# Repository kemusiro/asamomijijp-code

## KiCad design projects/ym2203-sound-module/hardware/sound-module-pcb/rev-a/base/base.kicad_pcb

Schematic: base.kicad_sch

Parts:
A1: Raspberry Pi Pico 2; A1
A2: AE-PCM5102A / I2S 48kHz; A2
C1: 47u 10V; C1
C2: 10u 10V; C2
C3: 100n; C3
C4: 100n; C4
C5: 2.2u X7R 10V; C5
C6: 2.2u X7R 10V; C6
C7: 1u X7R 10V; C7
C8: 100n; C8
C9: 100n; C9
C10: 100n; C10
C11: 10u 10V; C11
C12: 10u 10V; C12
C13: 10u 10V; C13
C14: 2.2n C0G; C14
C15: 2.2n C0G; C15
C16: 10u 10V; C16
C17: 100n; C17
C18: 100n; C18
C19: 4.7u BP 10V; C19
C20: 4.7u BP 10V; C20
C21: 47p; C21
C22: 4.7u BP 10V; C22
C23: 4.7u BP 10V; C23
C24: 47p; C24
C25: 100n; C25
C26: 4.7u BP 10V; C26
C27: 4.7u BP 10V; C27
D1: SS14 / A=+5V K=VSYS; D1
F1: PTC 0.5A hold; F1
H1: M3 / 3.2mm NPTH; H1
H2: M3 / 3.2mm NPTH; H2
H3: M3 / 3.2mm NPTH; H3
H4: M3 / 3.2mm NPTH; H4
H5: M3 / 3.2mm NPTH; H5
H6: M3 / 3.2mm NPTH; H6
H7: M3 / 3.2mm NPTH; H7
JHOST: HOST 3.3V I2C; JHOST
JLINE: TRS JACK / AMS-22 LINE IN; JLINE
JMOD: ESQ-125-58-L-D / socket; JMOD
JPOWER: MAIN INPUT / REGULATED DC 5V; JPOWER
JRUN: RESET SWITCH; JRUN
JVOL: EXTERNAL DUAL 10k A POT; JVOL
Q1: MMBT3904 / B1 E2 C3; Q1
R1: 4.7k; R1
R2: 4.7k; R2
R3: 4.7k; R3
R4: 4.7k; R4
R5: 10k; R5
R6: 47; R6
R7: 47; R7
R8: 47; R8
R9: 470; R9
R10: 470; R10
R11: 10k 1%; R11
R12: 10k 1%; R12
R13: 100k 1%; R13
R14: 100k 1%; R14
R15: 22k 1%; R15
R16: 100k 1%; R16
R17: 100k 1%; R17
R18: 22k 1%; R18
R19: 10k; R19
R20: 100k; R20
R21: 10k; R21
R22: 100k; R22
R23: 100; R23
R24: 100k; R24
R25: 100; R25
RN1: RKC8BD103J; RN1
RN2: RKC8BD103J; RN2
RN3: RKC4BD103J; RN3
RN4: RKC4BD103J; RN4
RN5: RKC4BD103J; RN5
TP1: +5V; TP1
TP2: +3V3; TP2
TP3: GND; TP3
TP4: ARM; TP4
TP5: RESET_N; TP5
TP6: AUX_SDA; TP6
TP7: AUX_SCL; TP7
TP8: DAC_L; TP8
TP9: DAC_R; TP9
TP10: VREF; TP10
TP11: MIX_L; TP11
TP12: MIX_R; TP12
U1: MCP23017-E/SP / 0x20; U1
U2: TC74HC08AP / 3.3V; U2
U3: MCP6022-I/P / reference; U3
U4: MCP6022-I/P / stereo mixer; U4
U5: CD74HC4053E / line mute; U5

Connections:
/+3V3: A1.36 (3V3 OUT), A2.1 (CPVDD), A2.8 (AVDD), A2.20 (DVDD), C2.1, C3.1, C4.1, C8.1, C9.1, C10.1, C11.1, C12.1, C13.1, JMOD.5 (+3V3), R1.2, R2.2, R3.2, R4.2, RN3.1 (COM), RN4.1 (COM), TP2.1, U1.9 (VDD), U2.14 (VCC)
/+5V: C1.1, C17.1, C18.1, C25.1, D1.2 (A), F1.2, JMOD.1 (+5V), JMOD.3 (+5V), R11.1, R21.1, TP1.1, U3.8 (VDD), U4.8 (VDD), U5.16 (VCC)
/A0: A1.11 (GP8 / A0), JMOD.15 (A0), RN2.3 (R2)
/A1: A1.12 (GP9 / A1), JMOD.17 (A1), RN2.4 (R3)
/ANALOG_L: C20.1, JMOD.42 (ANALOG_L)
/ANALOG_R: C23.1, JMOD.44 (ANALOG_R)
/ARM: A1.29 (GP22 / ARM), JMOD.24 (ARM), RN2.2 (R1), TP4.1, U2.1 (1A), U2.4 (2A), U2.9 (3A)
/AUX0: JMOD.39 (AUX0), RN2.8 (R7), U1.25 (GPA4)
/AUX1: JMOD.40 (AUX1), RN2.9 (R8), U1.26 (GPA5)
/AUX_SCL: A1.32 (GP27 / AUX_SCL), JMOD.33 (AUX_SCL), R4.1, TP7.1, U1.12 (SCL)
/AUX_SDA: A1.31 (GP26 / AUX_SDA), JMOD.32 (AUX_SDA), R3.1, TP6.1, U1.13 (SDA)
/CAPM: A2.4 (CAPM), C5.2
/CAPP: A2.2 (CAPP), C5.1
/CS_N: A1.17 (GP13 / CS_N), JMOD.19 (CS_N), RN4.2 (R1)
/D0: A1.1 (GP0 / D0), JMOD.7 (D0), RN1.2 (R1)
/D1: A1.2 (GP1 / D1), JMOD.8 (D1), RN1.3 (R2)
/D2: A1.4 (GP2 / D2), JMOD.9 (D2), RN1.4 (R3)
/D3: A1.5 (GP3 / D3), JMOD.10 (D3), RN1.5 (R4)
/D4: A1.6 (GP4 / D4), JMOD.11 (D4), RN1.6 (R5)
/D5: A1.7 (GP5 / D5), JMOD.12 (D5), RN1.7 (R6)
/D6: A1.9 (GP6 / D6), JMOD.13 (D6), RN1.8 (R7)
/D7: A1.10 (GP7 / D7), JMOD.14 (D7), RN1.9 (R8)
/DAC_ALLOW: RN2.6 (R5), U1.24 (GPA3), U2.5 (2B)
/DAC_BCK: A2.13 (BCK), R7.2
/DAC_DIN: A2.14 (DIN), R6.2
/DAC_L: A2.6 (OUTL), R9.1, TP8.1
/DAC_LRCK: A2.15 (LRCK), R8.2
/DAC_R: A2.7 (OUTR), R10.1, TP9.1
/DAC_XSMT: A2.17 (XSMT), R5.1, U2.6 (2Y)
/EXT_5V: F1.1, JPOWER.1 (EXT_5V)
/FM_AC_L: C19.2, R13.1
/FM_AC_R: C22.2, R16.1
/FM_CLK: A1.22 (GP17 / FM_CLK), JMOD.28 (FM_CLK), RN5.3 (R2)
/FM_L: C14.1, C19.1, R9.2
/FM_R: C15.1, C22.1, R10.2
/FM_SD: A1.21 (GP16 / FM_SD), JMOD.27 (FM_SD), RN5.2 (R1)
/FM_SH1: A1.24 (GP18 / FM_SH1), JMOD.29 (FM_SH1), RN5.4 (R3)
/FM_SH2: A1.25 (GP19 / FM_SH2), JMOD.30 (FM_SH2), RN5.5 (R4)
/GND: A1.3 (GND), A1.8 (GND), A1.13 (GND), A1.18 (GND), A1.23 (GND), A1.28 (GND), A1.33 (GND), A1.38 (GND), A2.3 (CPGND), A2.9 (AGND), A2.10 (DEMP), A2.11 (FLT), A2.12 (SCK), A2.16 (FMT), A2.19 (DGND), C1.2, C2.2, C3.2, C4.2, C6.2, C7.2, C8.2, C9.2, C10.2, C11.2, C12.2, C13.2, C14.2, C15.2, C16.2, C17.2, C18.2, C25.2, JHOST.1 (GND), JHOST.4 (GND), JLINE.3 (GND), JMOD.2 (GND), JMOD.4 (GND), JMOD.6 (GND), JMOD.16 (GND), JMOD.18 (GND), JMOD.22 (GND), JMOD.26 (GND), JMOD.31 (GND), JMOD.34 (GND), JMOD.41 (GND), JMOD.43 (GND), JMOD.45 (GND), JMOD.48 (GND), JMOD.49 (GND), JPOWER.2 (GND), JRUN.2 (GND), JVOL.3 (GND), JVOL.6 (GND), Q1.2 (E), R5.2, R12.2, R20.2, R22.2, R24.2, RN1.1 (COM), RN2.1 (COM), RN5.1 (COM), TP3.1, U1.5 (GPB4), U1.6 (GPB5), U1.7 (GPB6), U1.10 (VSS), U1.15 (A0), U1.16 (A1), U1.17 (A2), U2.7 (GND), U2.12 (4A), U2.13 (4B), U3.4 (VSS), U4.4 (VSS), U5.3 (Z1), U5.5 (Z0), U5.6 (INH), U5.7 (VEE), U5.8 (GND), U5.9 (C)
/HOST_SCL: A1.27 (GP21 / HOST_SCL), JHOST.3 (HOST_SCL), R2.1
/HOST_SDA: A1.26 (GP20 / HOST_SDA), JHOST.2 (HOST_SDA), R1.1
/I2S_BCLK: A1.15 (GP11 / I2S_BCLK), R7.1
/I2S_DATA: A1.14 (GP10 / I2S_DATA), R6.1
/I2S_LRCK: A1.16 (GP12 / I2S_LRCK), R8.1
/ID0: JMOD.35 (ID0), RN3.2 (R1), U1.1 (GPB0)
/ID1: JMOD.36 (ID1), RN3.3 (R2), U1.2 (GPB1)
/ID2: JMOD.37 (ID2), RN3.4 (R3), U1.3 (GPB2)
/LDOO: A2.18 (LDOO), C7.1
/LINE_ALLOW: RN2.7 (R6), U1.22 (GPA1), U2.10 (3B)
/LINE_L: JLINE.1 (LINE_L), R23.2
/LINE_R: JLINE.2 (LINE_R), R25.2
/LINE_RUN: R19.1, U2.8 (3Y)
/MIX_L: C21.1, R15.1, TP11.1, U4.1 (OUTA), U5.12 (X0)
/MIX_R: C24.1, R18.1, TP12.1, U4.7 (OUTB), U5.2 (Y0)
/MOD_AC_L: C20.2, R14.1
/MOD_AC_R: C23.2, R17.1
/MUTED_L: C26.1, U5.14 (X)
/MUTED_R: C27.1, U5.15 (Y)
/MUTE_5V: Q1.3 (C), R21.2, U5.10 (B), U5.11 (A)
/MUTE_BASE: Q1.1 (B), R19.2, R20.1
/OUT_AC_L: C26.2, JVOL.1 (OUT_AC_L), R22.1
/OUT_AC_R: C27.2, JVOL.4 (OUT_AC_R), R24.1
/PICO_RUN: A1.30 (RUN), JRUN.1 (PICO_RUN), U1.18 (RESET_N)
/PRESENT_N: JMOD.38 (PRESENT_N), RN3.5 (R4), U1.4 (GPB3)
/RD_N: A1.20 (GP15 / RD_N), JMOD.21 (RD_N), RN4.4 (R3)
/REF_RAW: C16.1, R11.2, R12.1, U3.3 (INA+)
/REF_SPARE: U3.6 (INB-), U3.7 (OUTB)
/RESET_N: JMOD.23 (RESET_N), TP5.1, U2.3 (1Y)
/RESET_RELEASE: RN2.5 (R4), U1.21 (GPA0), U2.2 (1B)
/STATUS: A1.34 (GP28 / STATUS), JMOD.25 (STATUS), RN4.5 (R4)
/SUM_L: C21.2, R13.2, R14.2, R15.2, U4.2 (INA-)
/SUM_R: C24.2, R16.2, R17.2, R18.2, U4.6 (INB-)
/VNEG: A2.5 (VNEG), C6.1
/VOL_L: JVOL.2 (VOL_L), R23.1
/VOL_R: JVOL.5 (VOL_R), R25.1
/VREF: TP10.1, U3.1 (OUTA), U3.2 (INA-), U3.5 (INB+), U4.3 (INA+), U4.5 (INB+), U5.1 (Y1), U5.13 (X1)
/VSYS: A1.39 (VSYS), D1.1 (K)
/WR_N: A1.19 (GP14 / WR_N), JMOD.20 (WR_N), RN4.3 (R2)

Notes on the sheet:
COMMON BASE / Pico 2 + stereo DAC + line mixer
Rev A / GPIO approved 2026-10-18 / Prototype - hardware untested / See README before manufacture
Labels of the same name are connected. Pin numbers are physical pins. Stereo line output to AMS-22.
CONTROLLER / IO
POWER / SAFETY
MODULE
DAC / CLOCK
ANALOG
PULLS / DECOUPLING / BUS / YM / FM / TEST

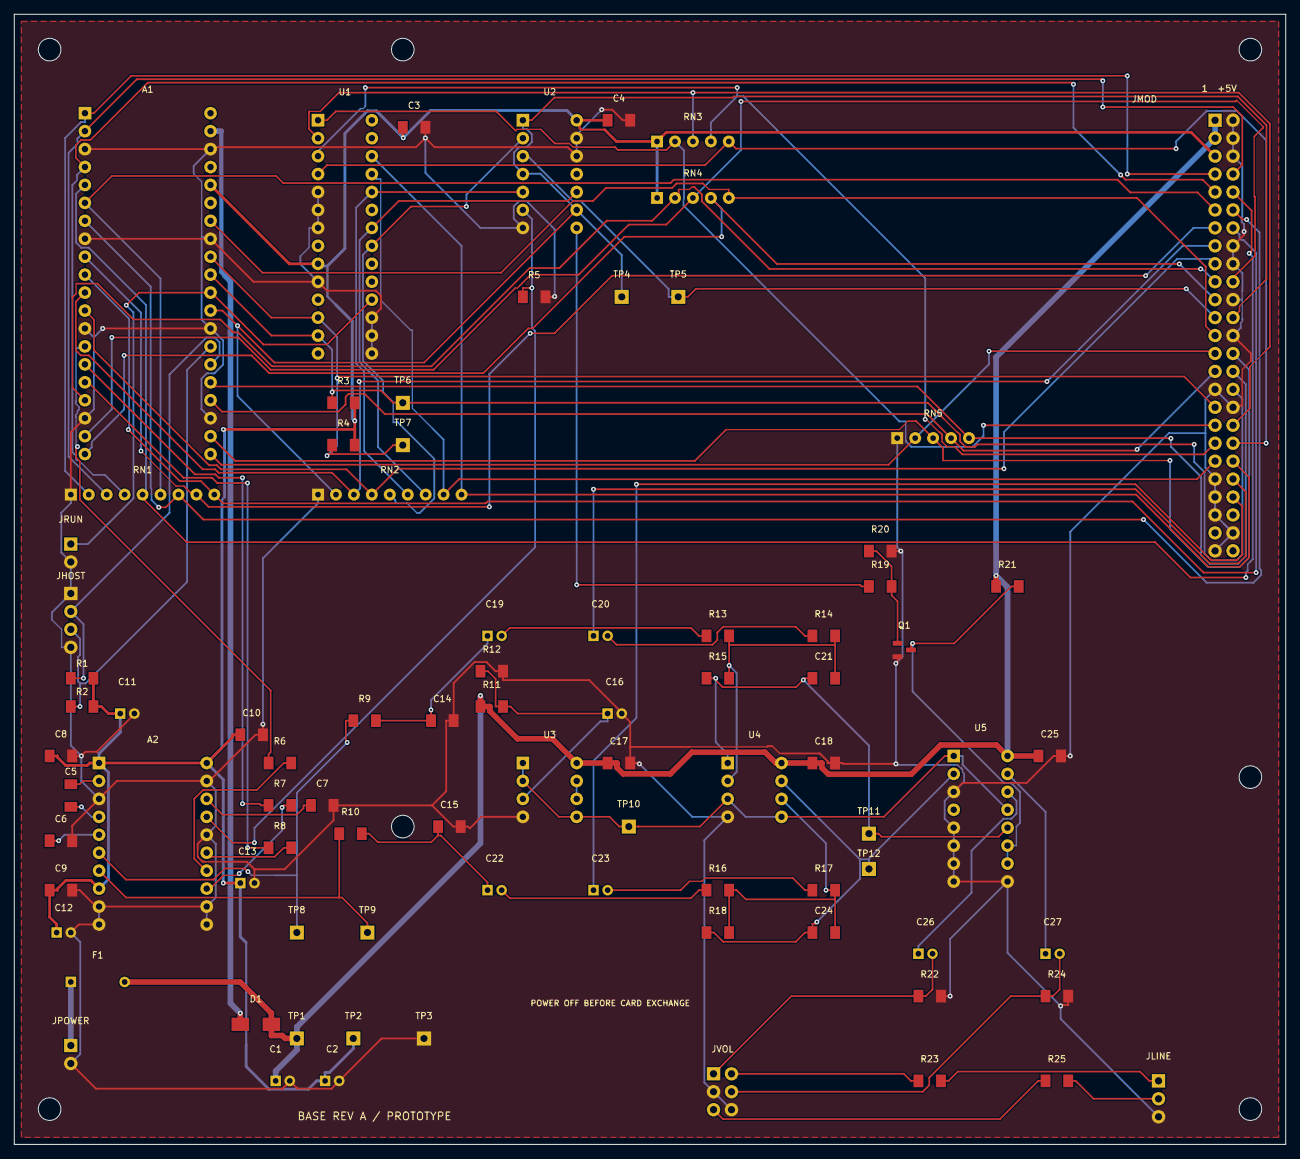
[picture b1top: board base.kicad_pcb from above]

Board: 2 copper layers, 180.0 x 160.0 mm, 92 parts (0 on the bottom side), 78 nets.

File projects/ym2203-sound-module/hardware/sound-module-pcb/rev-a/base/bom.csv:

reference,value,footprint,x_mm,y_mm,source,role
A1,Raspberry Pi Pico 2,SOUNDPCB:A1,10.0,14.0,https://datasheets.raspberrypi.com/pico/pico-2-datasheet.pdf,
JMOD,ESQ-125-58-L-D / socket,SOUNDPCB:JMOD,170.0,15.0,https://suddendocs.samtec.com/catalog_english/esq_th.pdf,Top-side 16.13mm female. Block contact 50 with an insulating key.
JHOST,HOST 3.3V I2C,SOUNDPCB:JHOST,8.0,82.0,,
JPOWER,MAIN INPUT / REGULATED DC 5V,SOUNDPCB:JPOWER,8.0,146.0,,"Required main supply: pin 1 = regulated +5V, pin 2 = GND. No reverse-polarity or overvoltage protection."
F1,PTC 0.5A hold,SOUNDPCB:F1,8.0,137.0,,
D1,SS14 / A=+5V K=VSYS,SOUNDPCB:D1,32.0,143.0,,Prevents Pico USB from feeding the external supply through VSYS
C1,47u 10V,SOUNDPCB:C1,37.0,151.0,,
C2,10u 10V,SOUNDPCB:C2,44.0,151.0,,
JRUN,RESET SWITCH,SOUNDPCB:JRUN,8.0,75.0,,
R1,4.7k,SOUNDPCB:R1,8.0,94.0,,Host pullups removable if already supplied externally
R2,4.7k,SOUNDPCB:R2,8.0,98.0,,Host pullups removable if already supplied externally
R3,4.7k,SOUNDPCB:R3,45.0,55.0,,Host pullups removable if already supplied externally
R4,4.7k,SOUNDPCB:R4,45.0,61.0,,Host pullups removable if already supplied externally
U1,MCP23017-E/SP / 0x20,SOUNDPCB:U1,43.0,15.0,https://akizukidenshi.com/catalog/g/g109486/,
C3,100n,SOUNDPCB:C3,55.0,16.0,,Place immediately beside supply pin
U2,TC74HC08AP / 3.3V,SOUNDPCB:U2,72.0,15.0,https://akizukidenshi.com/catalog/g/g114059/,
C4,100n,SOUNDPCB:C4,84.0,15.0,,Place immediately beside supply pin
RN1,RKC8BD103J,SOUNDPCB:RN1,8.0,68.0,https://akizukidenshi.com/catalog/g/g111910/,
RN2,RKC8BD103J,SOUNDPCB:RN2,43.0,68.0,https://akizukidenshi.com/catalog/g/g111910/,
RN3,RKC4BD103J,SOUNDPCB:RN3,91.0,18.0,https://akizukidenshi.com/catalog/g/g111909/,
RN4,RKC4BD103J,SOUNDPCB:RN4,91.0,26.0,https://akizukidenshi.com/catalog/g/g111909/,
RN5,RKC4BD103J,SOUNDPCB:RN5,125.0,60.0,https://akizukidenshi.com/catalog/g/g111909/,
R5,10k,SOUNDPCB:R5,72.0,40.0,,
A2,AE-PCM5102A / I2S 48kHz,SOUNDPCB:A2,12.0,106.0,https://akizukidenshi.com/catalog/g/g111836/,
R6,47,SOUNDPCB:R6,36.0,106.0,,
R7,47,SOUNDPCB:R7,36.0,112.0,,
R8,47,SOUNDPCB:R8,36.0,118.0,,
C5,2.2u X7R 10V,SOUNDPCB:C5,8.0,109.0,,
C6,2.2u X7R 10V,SOUNDPCB:C6,5.0,117.0,,
C7,1u X7R 10V,SOUNDPCB:C7,42.0,112.0,,
C8,100n,SOUNDPCB:C8,5.0,105.0,,Place immediately beside supply pin
C9,100n,SOUNDPCB:C9,5.0,124.0,,Place immediately beside supply pin
C10,100n,SOUNDPCB:C10,32.0,102.0,,Place immediately beside supply pin
C11,10u 10V,SOUNDPCB:C11,15.0,99.0,,
C12,10u 10V,SOUNDPCB:C12,6.0,130.0,,
C13,10u 10V,SOUNDPCB:C13,32.0,123.0,,
R9,470,SOUNDPCB:R9,48.0,100.0,,
C14,2.2n C0G,SOUNDPCB:C14,59.0,100.0,,
R10,470,SOUNDPCB:R10,46.0,116.0,,
C15,2.2n C0G,SOUNDPCB:C15,60.0,115.0,,
U3,MCP6022-I/P / reference,SOUNDPCB:U3,72.0,106.0,,
R11,10k 1%,SOUNDPCB:R11,66.0,98.0,,
R12,10k 1%,SOUNDPCB:R12,66.0,93.0,,
C16,10u 10V,SOUNDPCB:C16,84.0,99.0,,
C17,100n,SOUNDPCB:C17,84.0,106.0,,Place immediately beside supply pin
U4,MCP6022-I/P / stereo mixer,SOUNDPCB:U4,101.0,106.0,,
C18,100n,SOUNDPCB:C18,113.0,106.0,,Place immediately beside supply pin
C19,4.7u BP 10V,SOUNDPCB:C19,67.0,88.0,,
C20,4.7u BP 10V,SOUNDPCB:C20,82.0,88.0,,
R13,100k 1%,SOUNDPCB:R13,98.0,88.0,,
R14,100k 1%,SOUNDPCB:R14,113.0,88.0,,
R15,22k 1%,SOUNDPCB:R15,98.0,94.0,,
C21,47p,SOUNDPCB:C21,113.0,94.0,,
C22,4.7u BP 10V,SOUNDPCB:C22,67.0,124.0,,
C23,4.7u BP 10V,SOUNDPCB:C23,82.0,124.0,,
R16,100k 1%,SOUNDPCB:R16,98.0,124.0,,
R17,100k 1%,SOUNDPCB:R17,113.0,124.0,,
R18,22k 1%,SOUNDPCB:R18,98.0,130.0,,
C24,47p,SOUNDPCB:C24,113.0,130.0,,
U5,CD74HC4053E / line mute,SOUNDPCB:U5,133.0,105.0,https://akizukidenshi.com/catalog/g/g113266/,
C25,100n,SOUNDPCB:C25,145.0,105.0,,Place immediately beside supply pin
Q1,MMBT3904 / B1 E2 C3,SOUNDPCB:Q1,126.0,90.0,https://www.onsemi.com/pdf/datasheet/mmbt3904lt1-d.pdf,
R19,10k,SOUNDPCB:R19,121.0,81.0,,
R20,100k,SOUNDPCB:R20,121.0,76.0,,
R21,10k,SOUNDPCB:R21,139.0,81.0,,
C26,4.7u BP 10V,SOUNDPCB:C26,128.0,133.0,,
R22,100k,SOUNDPCB:R22,128.0,139.0,,
R23,100,SOUNDPCB:R23,128.0,151.0,,
C27,4.7u BP 10V,SOUNDPCB:C27,146.0,133.0,,
R24,100k,SOUNDPCB:R24,146.0,139.0,,
R25,100,SOUNDPCB:R25,146.0,151.0,,
JVOL,EXTERNAL DUAL 10k A POT,SOUNDPCB:JVOL,99.0,150.0,,Stereo 10k A pot: each channel HIGH/WIPER/LOW. Separate from mute.
JLINE,TRS JACK / AMS-22 LINE IN,SOUNDPCB:JLINE,162.0,151.0,,"External 3.5mm jack module, L=tip R=ring GND=sleeve. Not headphone power output."
TP1,+5V,SOUNDPCB:TP1,40.0,145.0,,
TP2,+3V3,SOUNDPCB:TP2,48.0,145.0,,
TP3,GND,SOUNDPCB:TP3,58.0,145.0,,
TP4,ARM,SOUNDPCB:TP4,86.0,40.0,,
TP5,RESET_N,SOUNDPCB:TP5,94.0,40.0,,
TP6,AUX_SDA,SOUNDPCB:TP6,55.0,55.0,,
TP7,AUX_SCL,SOUNDPCB:TP7,55.0,61.0,,
TP8,DAC_L,SOUNDPCB:TP8,40.0,130.0,,
TP9,DAC_R,SOUNDPCB:TP9,50.0,130.0,,
TP10,VREF,SOUNDPCB:TP10,87.0,115.0,,
TP11,MIX_L,SOUNDPCB:TP11,121.0,116.0,,
TP12,MIX_R,SOUNDPCB:TP12,121.0,121.0,,
H1,M3 / 3.2mm NPTH,SOUNDPCB:H1,55.0,5.0,,
H2,M3 / 3.2mm NPTH,SOUNDPCB:H2,175.0,5.0,,
H3,M3 / 3.2mm NPTH,SOUNDPCB:H3,55.0,115.0,,
H4,M3 / 3.2mm NPTH,SOUNDPCB:H4,175.0,108.0,,
H5,M3 / 3.2mm NPTH,SOUNDPCB:H5,5.0,5.0,,
H6,M3 / 3.2mm NPTH,SOUNDPCB:H6,5.0,155.0,,
H7,M3 / 3.2mm NPTH,SOUNDPCB:H7,175.0,155.0,,

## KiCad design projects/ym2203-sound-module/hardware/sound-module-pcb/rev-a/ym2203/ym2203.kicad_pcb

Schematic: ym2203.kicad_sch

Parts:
A1: AE-LLCNV-LVC8T245; A1
A2: AE-LLCNV-LVC8T245; A2
C1: 100n; C1
C2: 10u 10V; C2
C3: 100n; C3
C4: 100n; C4
C5: 100n; C5
C6: 100n; C6
C7: 100n; C7
C8: 100n; C8
C9: 100n; C9
C10: 100n; C10
C11: 10u 10V; C11
C12: 4.7u BP 10V; C12
C13: 4.7u BP 10V; C13
C14: 4.7u BP 10V; C14
C15: 47p; C15
C16: 4.7u BP 10V; C16
C17: 4.7u BP 10V; C17
H1: M3 / 3.2mm NPTH; H1
H2: M3 / 3.2mm NPTH; H2
H3: M3 / 3.2mm NPTH; H3
H4: M3 / 3.2mm NPTH; H4
JMOD: TSW-125-07-L-D / header; JMOD
R1: 4.7k; R1
R2: 10k; R2
R3: 10k; R3
R4: 10k; R4
R5: 47; R5
R6: 47; R6
R7: 10k 1%; R7
R8: 10k 1%; R8
R9: 100k 1%; R9
R10: 100k 1%; R10
R11: 100k 1%; R11
R12: 100k 1%; R12
R13: 100k; R13
R14: 100k; R14
RN1: RKC8BD103J; RN1
RN2: RKC4BD103J; RN2
RN3: RKC8BD102J; RN3
TP1: +5V; TP1
TP2: +3V3; TP2
TP3: GND; TP3
TP4: CLK4; TP4
TP5: Y_SD; TP5
TP6: Y_CLK; TP6
TP7: Y_SH; TP7
TP8: Y_IRQ; TP8
TP9: OE_WRITE_N; TP9
TP10: OE_READ_N; TP10
TP11: SSG_MIX; TP11
U1: YM2203C / DIP40; U1
U2: 74LCX245FT / 3.3V; U2
U3: 74LCX245FT / 3.3V; U3
U4: TC74HC04AP / 3.3V; U4
U5: TC74HC00AP / 3.3V; U5
U6: TC74HC32AP / 3.3V; U6
U7: TC74HC74AP / 5V; U7
U8: MCP6022-I/P / SSG mixer; U8
X1: 8MHz 5V oscillator; X1

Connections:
/+3V3: A1.1 (VA), A1.3 (DIR A>B), A1.24 (VA), A2.1 (VA), A2.3 (DIR A>B), A2.24 (VA), C3.1, C4.1, C5.1, C6.1, C7.1, JMOD.5 (+3V3), R2.2, R4.2, TP2.1, U2.1 (DIR A>B), U2.20 (VCC), U3.1 (DIR A>B), U3.20 (VCC), U4.14 (VCC), U5.14 (VCC), U6.14 (VCC)
/+5V: A1.23 (VB), A2.23 (VB), C1.1, C2.1, C8.1, C9.1, C10.1, JMOD.1 (+5V), JMOD.3 (+5V), R7.1, RN2.1 (COM), TP1.1, U1.21 (VDD), U7.1 (CLR1_N), U7.4 (PRE1_N), U7.10 (PRE2_N), U7.13 (CLR2_N), U7.14 (VCC), U8.8 (VDD), X1.8 (VCC)
/A0: A2.4 (A1), JMOD.15 (A0)
/ANALOG_L: C16.2, JMOD.42 (ANALOG_L), R13.1
/ANALOG_R: C17.2, JMOD.44 (ANALOG_R), R14.1
/ARM: JMOD.24 (ARM), R3.1, U4.1 (1A), U5.1 (1A), U5.4 (2A)
/CLK4: R6.2, TP4.1, U1.38 (PHI_M 4MHz)
/CLK8: R5.2, U7.3 (CLK1)
/CLK_FB: U7.2 (D1), U7.6 (Q1_N)
/CS_N: JMOD.19 (CS_N), U6.1 (CS_N)
/D0: A1.4 (A1), JMOD.7 (D0), U2.18 (B1)
/D1: A1.5 (A2), JMOD.8 (D1), U2.17 (B2)
/D2: A1.6 (A3), JMOD.9 (D2), U2.16 (B3)
/D3: A1.7 (A4), JMOD.10 (D3), U2.15 (B4)
/D4: A1.8 (A5), JMOD.11 (D4), U2.14 (B5)
/D5: A1.9 (A6), JMOD.12 (D5), U2.13 (B6)
/D6: A1.10 (A7), JMOD.13 (D6), U2.12 (B7)
/D7: A1.11 (A8), JMOD.14 (D7), U2.11 (B8)
/DIV4: R6.1, U7.5 (Q1)
/FM_CLK: JMOD.28 (FM_CLK), U3.17 (B2)
/FM_SD: JMOD.27 (FM_SD), U3.18 (B1)
/FM_SH1: JMOD.29 (FM_SH1), U3.16 (B3)
/GND: A1.12 (GND), A1.13 (GND), A1.22 (GND), A2.2 (OE_N), A2.9 (A6), A2.10 (A7), A2.11 (A8), A2.12 (GND), A2.13 (GND), A2.22 (GND), C1.2, C2.2, C3.2, C4.2, C5.2, C6.2, C7.2, C8.2, C9.2, C10.2, C11.2, JMOD.2 (GND), JMOD.4 (GND), JMOD.6 (GND), JMOD.16 (GND), JMOD.18 (GND), JMOD.22 (GND), JMOD.26 (GND), JMOD.31 (GND), JMOD.34 (GND), JMOD.36 (GND), JMOD.37 (GND), JMOD.38 (GND), JMOD.41 (GND), JMOD.43 (GND), JMOD.45 (GND), JMOD.48 (GND), JMOD.49 (GND), R1.2, R3.2, R8.2, R13.2, R14.2, RN1.1 (COM), RN3.1 (COM), TP3.1, U1.1 (GND), U1.17 (GND), U2.10 (GND), U3.6 (A5), U3.7 (A6), U3.8 (A7), U3.9 (A8), U3.10 (GND), U3.19 (OE_N), U4.5 (3A), U4.7 (GND), U4.9 (4A), U4.11 (5A), U4.13 (6A), U5.7 (GND), U5.9 (3A), U5.10 (3B), U5.12 (4A), U5.13 (4B), U6.7 (GND), U6.12 (4A), U6.13 (4B), U7.7 (GND), U7.11 (CLK2), U7.12 (D2), U8.4 (VSS), X1.4 (GND)
/NOT_ARM: U4.2 (1Y), U6.2 (NOT_ARM), U6.5 (NOT_ARM), U6.10 (NOT_ARM)
/NOT_RD_N: U4.4 (2Y), U5.5 (2B)
/OE_READ_N: R4.1, TP10.1, U2.19 (OE_N), U5.6 (2Y)
/OE_WRITE_N: A1.2 (OE_N), TP9.1, U5.3 (1Y)
/OSC8: R5.1, X1.5 (OUT)
/RD_N: JMOD.21 (RD_N), U4.3 (2A), U5.2 (1B), U6.9 (RD_N)
/REF_CARD_RAW: C11.1, R7.2, R8.1, U8.3 (INA+)
/RESET_N: A2.5 (A2), JMOD.23 (RESET_N)
/SAFE_CS_N: A2.6 (A3), U6.3 (SAFE_CS_N)
/SAFE_RD_N: A2.8 (A5), U6.8 (SAFE_RD_N)
/SAFE_WR_N: A2.7 (A4), U6.6 (SAFE_WR_N)
/SSG_A: C12.1, RN3.2 (R1), U1.20 (SSG_A)
/SSG_A_AC: C12.2, R9.1
/SSG_B: C13.1, RN3.3 (R2), U1.19 (SSG_B)
/SSG_B_AC: C13.2, R10.1
/SSG_C: C14.1, RN3.4 (R3), U1.18 (SSG_C)
/SSG_C_AC: C14.2, R11.1
/SSG_MIX: C15.2, C16.1, C17.1, R12.2, TP11.1, U8.7 (OUTB)
/SSG_SUM: C15.1, R9.2, R10.2, R11.2, R12.1, U8.6 (INB-)
/STATUS: JMOD.25 (STATUS), U3.15 (B4)
/VREF_CARD: U8.1 (OUTA), U8.2 (INA-), U8.5 (INB+)
/WR_N: JMOD.20 (WR_N), U6.4 (WR_N)
/Y_A0: A2.21 (B1), U1.37 (A0)
/Y_CLK: TP6.1, U1.39 (CLK), U3.3 (A2)
/Y_CS_N: A2.19 (B3), RN2.2 (R1), U1.34 (CS_N)
/Y_D0: A1.21 (B1), RN1.2 (R1), U1.40 (D0), U2.2 (A1)
/Y_D1: A1.20 (B2), RN1.3 (R2), U1.2 (D1), U2.3 (A2)
/Y_D2: A1.19 (B3), RN1.4 (R3), U1.3 (D2), U2.4 (A3)
/Y_D3: A1.18 (B4), RN1.5 (R4), U1.4 (D3), U2.5 (A4)
/Y_D4: A1.17 (B5), RN1.6 (R5), U1.5 (D4), U2.6 (A5)
/Y_D5: A1.16 (B6), RN1.7 (R6), U1.6 (D5), U2.7 (A6)
/Y_D6: A1.15 (B7), RN1.8 (R7), U1.7 (D6), U2.8 (A7)
/Y_D7: A1.14 (B8), RN1.9 (R8), U1.8 (D7), U2.9 (A8)
/Y_IRQ: R2.1, TP8.1, U1.25 (IRQ_N), U3.5 (A4)
/Y_RD_N: A2.17 (B5), RN2.4 (R3), U1.36 (RD_N)
/Y_RESET_N: A2.20 (B2), R1.1, U1.24 (RESET_N)
/Y_SD: TP5.1, U1.23 (SD), U3.2 (A1)
/Y_SH: TP7.1, U1.22 (SH), U3.4 (A3)
/Y_WR_N: A2.18 (B4), RN2.3 (R2), U1.35 (WR_N)

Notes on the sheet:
YM2203C CARD / 4MHz / ID=001
Rev A / GPIO approved 2026-10-18 / Prototype - hardware untested / See README before manufacture
Labels of the same name are connected. Pin numbers are physical pins. Stereo line output to AMS-22.
BUS
FM / SAFETY
MODULE
ANALOG / CLOCK
PULLS / DECOUPLING / TEST

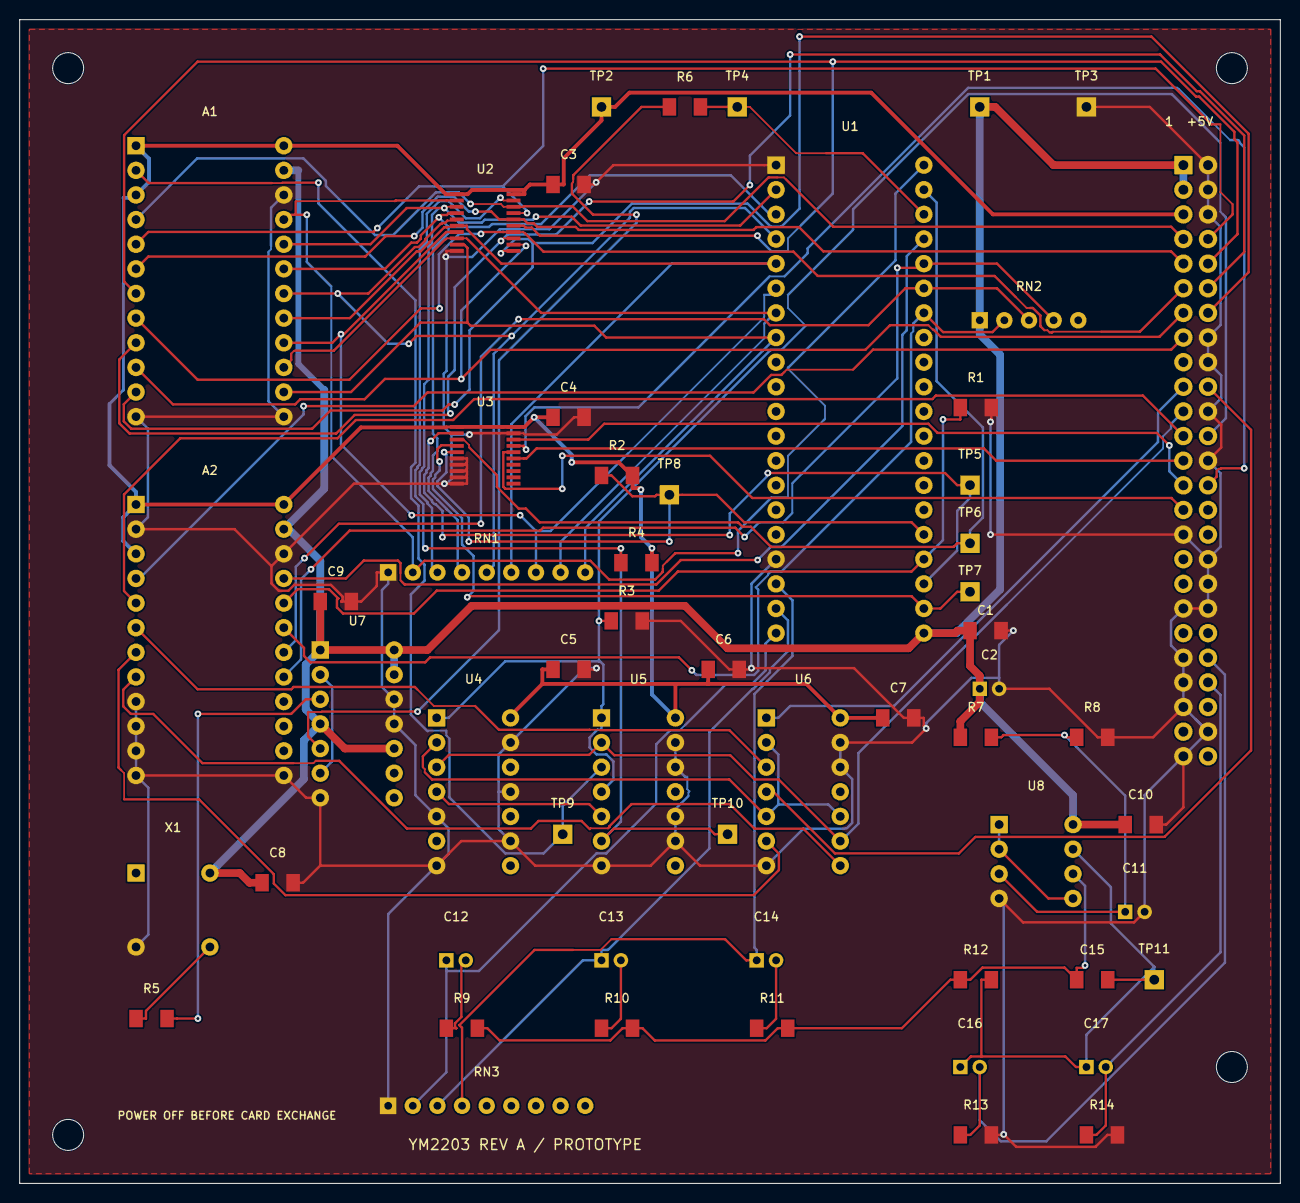
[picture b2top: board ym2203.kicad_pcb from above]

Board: 2 copper layers, 130.0 x 120.0 mm, 61 parts (1 on the bottom side), 62 nets.

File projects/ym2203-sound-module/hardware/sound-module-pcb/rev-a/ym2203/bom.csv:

reference,value,footprint,x_mm,y_mm,source,role
JMOD,TSW-125-07-L-D / header,SOUNDPCB:JMOD,120.0,15.0,https://suddendocs.samtec.com/catalog_english/tsw_th.pdf,Bottom male; remove contact 50. 19mm face-to-face spacing gives 5.51mm insertion.
U1,YM2203C / DIP40,SOUNDPCB:U1,78.0,15.0,https://www.bitsavers.org/components/yamaha/YM2203_198911.pdf,
C1,100n,SOUNDPCB:C1,98.0,63.0,,Place immediately beside supply pin
C2,10u 10V,SOUNDPCB:C2,99.0,69.0,,
A1,AE-LLCNV-LVC8T245,SOUNDPCB:A1,12.0,13.0,https://akizukidenshi.com/catalog/g/g115778/,
A2,AE-LLCNV-LVC8T245,SOUNDPCB:A2,12.0,50.0,https://akizukidenshi.com/catalog/g/g115778/,
U2,74LCX245FT / 3.3V,SOUNDPCB:U2,48.0,18.0,https://akizukidenshi.com/goodsaffix/74LCX245FT_datasheet_ja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,
C3,100n,SOUNDPCB:C3,55.0,17.0,,Place immediately beside supply pin
U3,74LCX245FT / 3.3V,SOUNDPCB:U3,48.0,42.0,https://akizukidenshi.com/goodsaffix/74LCX245FT_datasheet_ja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,
C4,100n,SOUNDPCB:C4,55.0,41.0,,Place immediately beside supply pin
U4,TC74HC04AP / 3.3V,SOUNDPCB:U4,43.0,72.0,https://akizukidenshi.com/catalog/g/g114058/,
U5,TC74HC00AP / 3.3V,SOUNDPCB:U5,60.0,72.0,https://akizukidenshi.com/catalog/g/g110856/,
U6,TC74HC32AP / 3.3V,SOUNDPCB:U6,77.0,72.0,https://akizukidenshi.com/catalog/g/g112877/,
C5,100n,SOUNDPCB:C5,55.0,67.0,,Place immediately beside supply pin
C6,100n,SOUNDPCB:C6,71.0,67.0,,Place immediately beside supply pin
C7,100n,SOUNDPCB:C7,89.0,72.0,,Place immediately beside supply pin
RN1,RKC8BD103J,SOUNDPCB:RN1,38.0,57.0,https://akizukidenshi.com/catalog/g/g111910/,
RN2,RKC4BD103J,SOUNDPCB:RN2,99.0,31.0,https://akizukidenshi.com/catalog/g/g111909/,
R1,4.7k,SOUNDPCB:R1,97.0,40.0,,
R2,10k,SOUNDPCB:R2,60.0,47.0,,
R3,10k,SOUNDPCB:R3,61.0,62.0,,
R4,10k,SOUNDPCB:R4,62.0,56.0,,
X1,8MHz 5V oscillator,SOUNDPCB:X1,12.0,88.0,https://akizukidenshi.com/goodsaffix/osc.pdf,
C8,100n,SOUNDPCB:C8,25.0,89.0,,Place immediately beside supply pin
R5,47,SOUNDPCB:R5,12.0,103.0,,
U7,TC74HC74AP / 5V,SOUNDPCB:U7,31.0,65.0,https://akizukidenshi.com/goodsaffix/TC74HC74AP_datasheet_ja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,
C9,100n,SOUNDPCB:C9,31.0,60.0,,Place immediately beside supply pin
R6,47,SOUNDPCB:R6,67.0,9.0,,
U8,MCP6022-I/P / SSG mixer,SOUNDPCB:U8,101.0,83.0,,
C10,100n,SOUNDPCB:C10,114.0,83.0,,Place immediately beside supply pin
R7,10k 1%,SOUNDPCB:R7,97.0,74.0,,
R8,10k 1%,SOUNDPCB:R8,109.0,74.0,,
C11,10u 10V,SOUNDPCB:C11,114.0,92.0,,
C12,4.7u BP 10V,SOUNDPCB:C12,44.0,97.0,,
R9,100k 1%,SOUNDPCB:R9,44.0,104.0,,
C13,4.7u BP 10V,SOUNDPCB:C13,60.0,97.0,,
R10,100k 1%,SOUNDPCB:R10,60.0,104.0,,
C14,4.7u BP 10V,SOUNDPCB:C14,76.0,97.0,,
R11,100k 1%,SOUNDPCB:R11,76.0,104.0,,
RN3,RKC8BD102J,SOUNDPCB:RN3,38.0,112.0,https://akizukidenshi.com/catalog/g/g113722/,
R12,100k 1%,SOUNDPCB:R12,97.0,99.0,,
C15,47p,SOUNDPCB:C15,109.0,99.0,,
C16,4.7u BP 10V,SOUNDPCB:C16,97.0,108.0,,
R13,100k,SOUNDPCB:R13,97.0,115.0,,
C17,4.7u BP 10V,SOUNDPCB:C17,110.0,108.0,,
R14,100k,SOUNDPCB:R14,110.0,115.0,,
TP1,+5V,SOUNDPCB:TP1,99.0,9.0,,
TP2,+3V3,SOUNDPCB:TP2,60.0,9.0,,
TP3,GND,SOUNDPCB:TP3,110.0,9.0,,
TP4,CLK4,SOUNDPCB:TP4,74.0,9.0,,
TP5,Y_SD,SOUNDPCB:TP5,98.0,48.0,,
TP6,Y_CLK,SOUNDPCB:TP6,98.0,54.0,,
TP7,Y_SH,SOUNDPCB:TP7,98.0,59.0,,
TP8,Y_IRQ,SOUNDPCB:TP8,67.0,49.0,,
TP9,OE_WRITE_N,SOUNDPCB:TP9,56.0,84.0,,
TP10,OE_READ_N,SOUNDPCB:TP10,73.0,84.0,,
TP11,SSG_MIX,SOUNDPCB:TP11,117.0,99.0,,
H1,M3 / 3.2mm NPTH,SOUNDPCB:H1,5.0,5.0,,
H2,M3 / 3.2mm NPTH,SOUNDPCB:H2,125.0,5.0,,
H3,M3 / 3.2mm NPTH,SOUNDPCB:H3,5.0,115.0,,
H4,M3 / 3.2mm NPTH,SOUNDPCB:H4,125.0,108.0,,
